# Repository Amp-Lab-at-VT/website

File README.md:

# Developing the Amp Lab website

Hello student of faculty! Welcome to the Amp Lab website repository. This is a simple static website built NextJS. It is hosted through Github Pages, making it easy to deploy and maintain. This document will guide you through the process of setting up your local development environment, making changes to the website, and deploying those changes.

You have two options for working on this locally: Docker, or Node. The following will describe both methods

# Using Docker

1. **Install Docker**: If you don't have Docker installed, download and install it from the [Docker website](https://www.docker.com/get-started).
2. **Clone the repository**: Open a terminal and run the following command to clone the repository
3. **Build and Run the Docker container**: Navigate to the cloned repository and run the following command to build and run the Docker container:
   ```bash
   docker-compose up --build
   ```

   And that's it!

# Using Node

1. **Install NVM**: If you don't have NVM installed, download and install it from the [NVM for Windows website](https://github.com/coreybutler/nvm-windows)
2.**Restart your computer to apply the changes**: After installing NVM, restart your computer to ensure that the changes take effect.
2. **Install Node**: Open a terminal and run the following command to install Node:
   ```bash
   nvm install 22
   nvm use 22
   ```

# Installing Dependencies
1. **Clone the repository**: Open a terminal and run the following command to clone the repository
   ```bash
   npm install
   ```

# Branch Before You Start Working
1. **Create a new branch**: Before making any changes, create a new branch for your work. This will help keep the main branch clean and allow for easier collaboration. Run the following command to create a new branch:
   ```bash
   git checkout -b your-branch-name
   ```

# Start the development server: Run the following command to start the development server:
   ```bash
   npm run dev
   ```

   This will start the development server and open the website in your default web browser. You can now make changes to the code and see them reflected in real-time.

# Pushing and PR Process
1. **Commit your changes**: After making changes, commit them to your branch with a descriptive message. Run the following command to commit your changes:
   ```bash
   git add .
   git commit -m "Your commit message"
   ```
2. Push your changes: Push your changes to the remote repository with the following command:
   ```bash
   git push origin your-branch-name
   ```
3. **Create a pull request**: Go to the GitHub repository and create a pull request from your branch to the main branch. This will allow others to review your changes before merging them into the main branch.
4. **Review and merge**: Once your pull request is approved, you can merge it into the main branch. This will update the main branch with your changes.

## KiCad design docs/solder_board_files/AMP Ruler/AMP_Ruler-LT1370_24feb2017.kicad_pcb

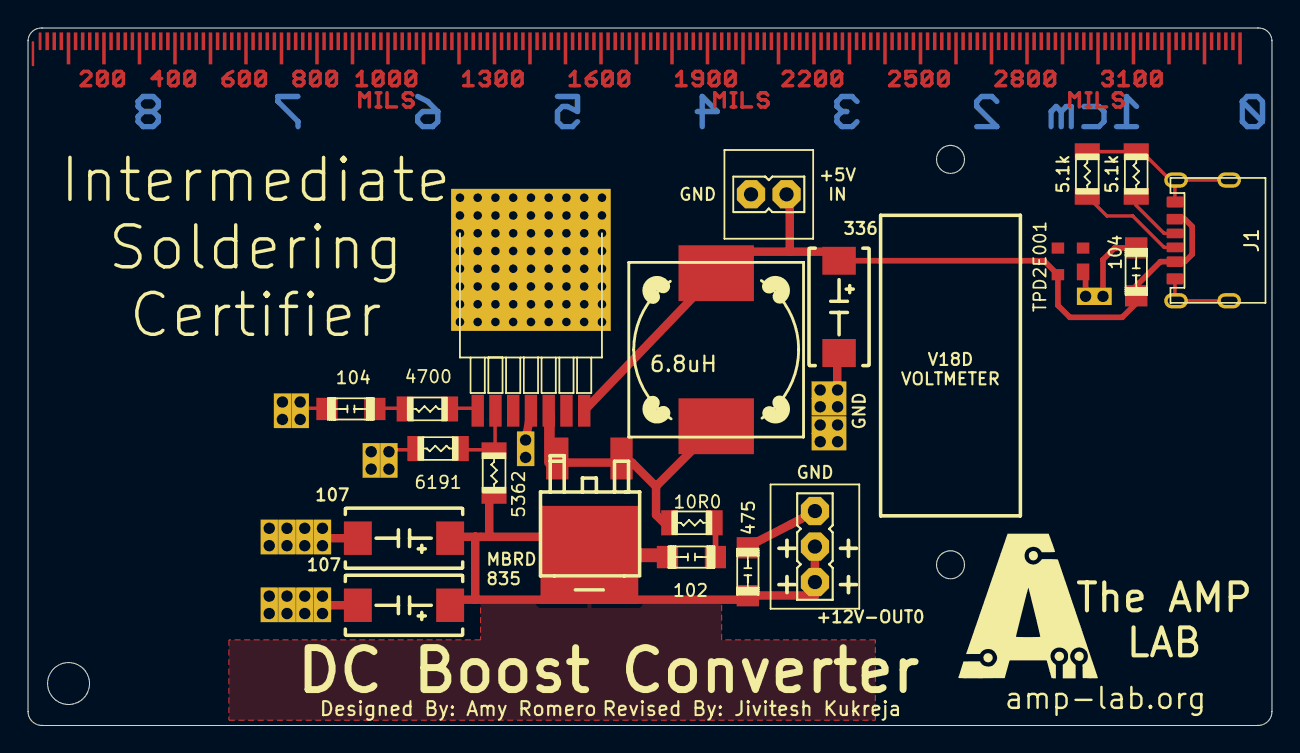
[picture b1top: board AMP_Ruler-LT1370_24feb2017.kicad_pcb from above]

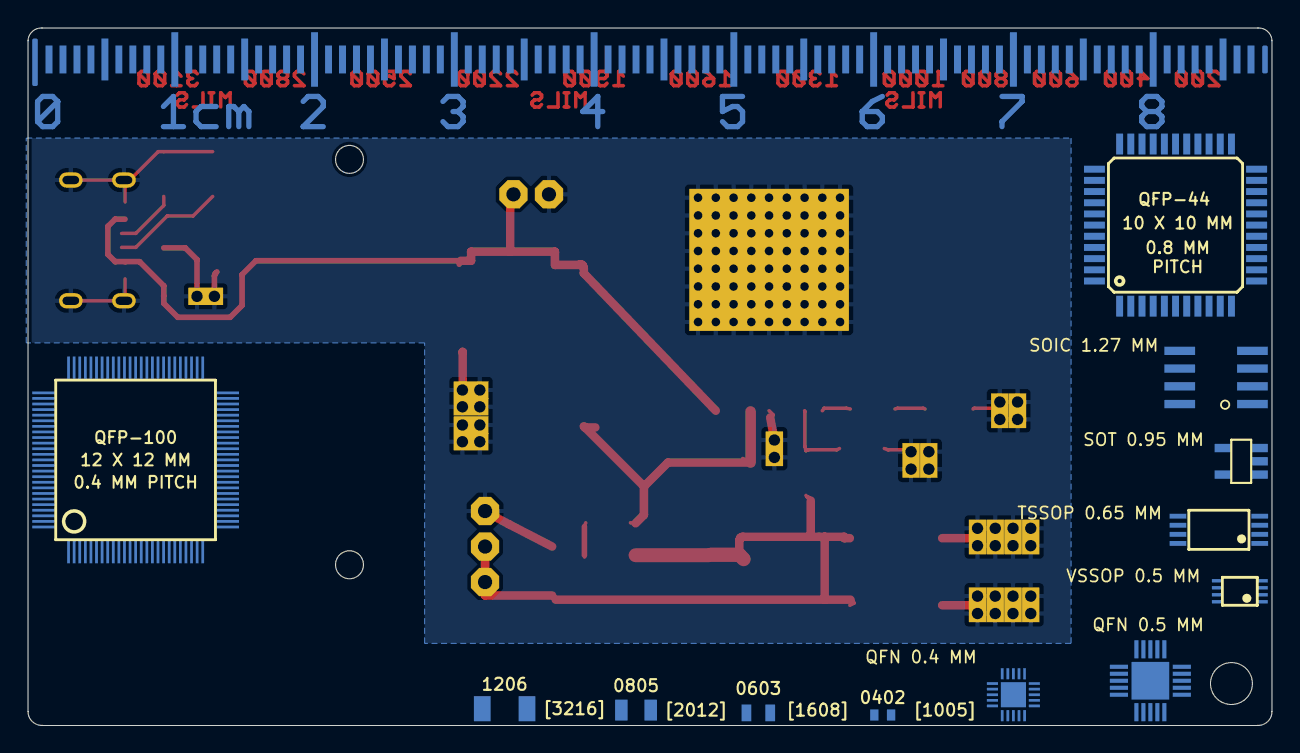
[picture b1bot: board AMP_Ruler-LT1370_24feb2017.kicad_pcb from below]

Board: 2 copper layers, 89.0 x 49.9 mm, 55 parts (19 on the bottom side), 10 nets.

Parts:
+12V-OUT0: FE03-1-TB
---0: DIODE-DPAK
@HOLE0, @HOLE1, @HOLE2: (no value)
C1: 336; C-2917
C2, C3: 107; C-2917
C4, C5: 104; C-1206
C6: 475; C-1206
C7: 102; C-1206
GND0: DOUBLE_RF_VIA
J1: USB_C_Receptacle_USB2.0; GCTUSB4125GFA190
L1: 6.8uH; SRR1240
R1: 6191; R1206
R2: 5362; R1206
R3, R6: 5.1k; R1206
R4: 4700; R1206
R5: 10R0; R1206
U1: LT1370
U$1: SOIC 1.27 MM; SOIC-8
U$2: SOT 0.95 MM; SOT23-5
U$3: TSSOP 0.65 MM; TSSOP-8
U$4: VSSOP 0.5 MM; VSSOP-8
U$5: QFP-44-10X10; QFP-44
U$6: QFP-100-12X12; QFP-100
U$8: QFN 0.5 MM; QFN-20-4X4
U$9: QFN 0.4 MM; QFN-20-3X3
U$10: 1206; R1206
U$11: 0805; R0805
U$12: 0603; R0603
U$13: 0402; R0402
U$14: MMRULER
U$15: MILRULER
U$16, U$17, U$18, U$19, U$20, U$21, U$22, U$23, U$24, U$25, U$26, U$27, U$32, U$33, U$34, U$35, U$37: DOUBLE_RF_VIA
U$36: TPD2E001; SOT-143
U$38: FE02-TB

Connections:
/AMP_Ruler-LT1370_24feb2017_3/VIN: C1.P$1, C4.P$2, J1.A9 (VBUS), J1.B9 (VBUS), L1.1, U1.P$7 (VIN), U$36.4 (+), U$38.1
/AMP_Ruler-LT1370_24feb2017_3/VOUT: +12V-OUT0.1, +12V-OUT0.2, ---0.P$4, C2.P$1, C3.P$1, C6.P$2, C7.P$1, R2.2
GND: +12V-OUT0.3, C1.P$2, C2.P$2, C3.P$2, C4.P$1, C5.P$2, C6.P$1, GND0.1, GND0.2 (P1), J1.A12 (GND), J1.B12 (GND), J1.S1 (SHIELD), R1.1, R3.2, R6.2, U1.P$4 (GND), U1.P$8 (GNDT), U1.P$9 (GNDT), U1.P$10 (GNDT), U1.P$11 (GNDT), U1.P$12 (GNDT), U1.P$13 (GNDT), U1.P$14 (GNDT), U1.P$15 (GNDT), U1.P$16 (GNDT), U1.P$17 (GNDT), U1.P$18 (GNDT), U1.P$19 (GNDT), U1.P$20 (GNDT), U1.P$21 (GNDT), U1.P$22 (GNDT), U1.P$23 (GNDT), U1.P$24 (GNDT), U1.P$25 (GNDT), U1.P$26 (GNDT), U1.P$27 (GNDT), U1.P$28 (GNDT), U1.P$29 (GNDT), U1.P$30 (GNDT), U1.P$31 (GNDT), U1.P$32 (GNDT), U1.P$33 (GNDT), U1.P$34 (GNDT), U1.P$35 (GNDT), U1.P$36 (GNDT), U1.P$37 (GNDT), U1.P$38 (GNDT), U1.P$39 (GNDT), U1.P$40 (GNDT), U1.P$41 (GNDT), U1.P$42 (GNDT), U1.P$43 (GNDT), U1.P$44 (GNDT), U1.P$45 (GNDT), U1.P$46 (GNDT), U1.P$47 (GNDT), U1.P$48 (GNDT), U1.P$49 (GNDT), U1.P$50 (GNDT), U1.P$51 (GNDT), U1.P$52 (GNDT), U1.P$53 (GNDT), U1.P$54 (GNDT), U1.P$55 (GNDT), U1.P$56 (GNDT), U1.P$57 (GNDT), U1.P$58 (GNDT), U1.P$59 (GNDT), U1.P$60 (GNDT), U1.P$61 (GNDT), U1.P$62 (GNDT), U1.P$63 (GNDT), U1.P$64 (GNDT), U1.P$65 (GNDT), U1.P$66 (GNDT), U1.P$67 (GNDT), U1.P$68 (GNDT), U1.P$69 (GNDT), U1.P$70 (GNDT), U1.P$71 (GNDT), U1.P$72 (GNDT), U1.P$73 (GNDT), U1.P$75 (GNDT), U1.P$76 (GNDT), U1.P$77 (GNDT), U1.P$78 (GNDT), U1.P$79 (GNDT), U1.P$80 (GNDT), U$16.1, U$16.2 (P1), U$17.1, U$17.2 (P1), U$18.1, U$18.2 (P1), U$19.1, U$19.2 (P1), U$20.1, U$20.2 (P1), U$21.1, U$21.2 (P1), U$22.1, U$22.2 (P1), U$23.1, U$23.2 (P1), U$24.1, U$24.2 (P1), U$25.1, U$25.2 (P1), U$26.1, U$26.2 (P1), U$27.1, U$27.2 (P1), U$32.1, U$32.2 (P1), U$33.1, U$33.2 (P1), U$34.1, U$34.2 (P1), U$35.1, U$35.2 (P1), U$36.1 (-), U$37.1, U$37.2 (P1), U$38.2
unnamed: ---0.P$1, ---0.P$3, L1.2, R5.1, U1.P$5 (VSW)
unnamed: C5.P$1, R4.2
unnamed: C7.P$2, R5.2
unnamed: J1.A5 (CC1), R6.1
unnamed: J1.B5 (CC2), R3.1
unnamed: R1.2, R2.1, U1.P$2 (FB)
unnamed: R4.1, U1.P$1 (VC)

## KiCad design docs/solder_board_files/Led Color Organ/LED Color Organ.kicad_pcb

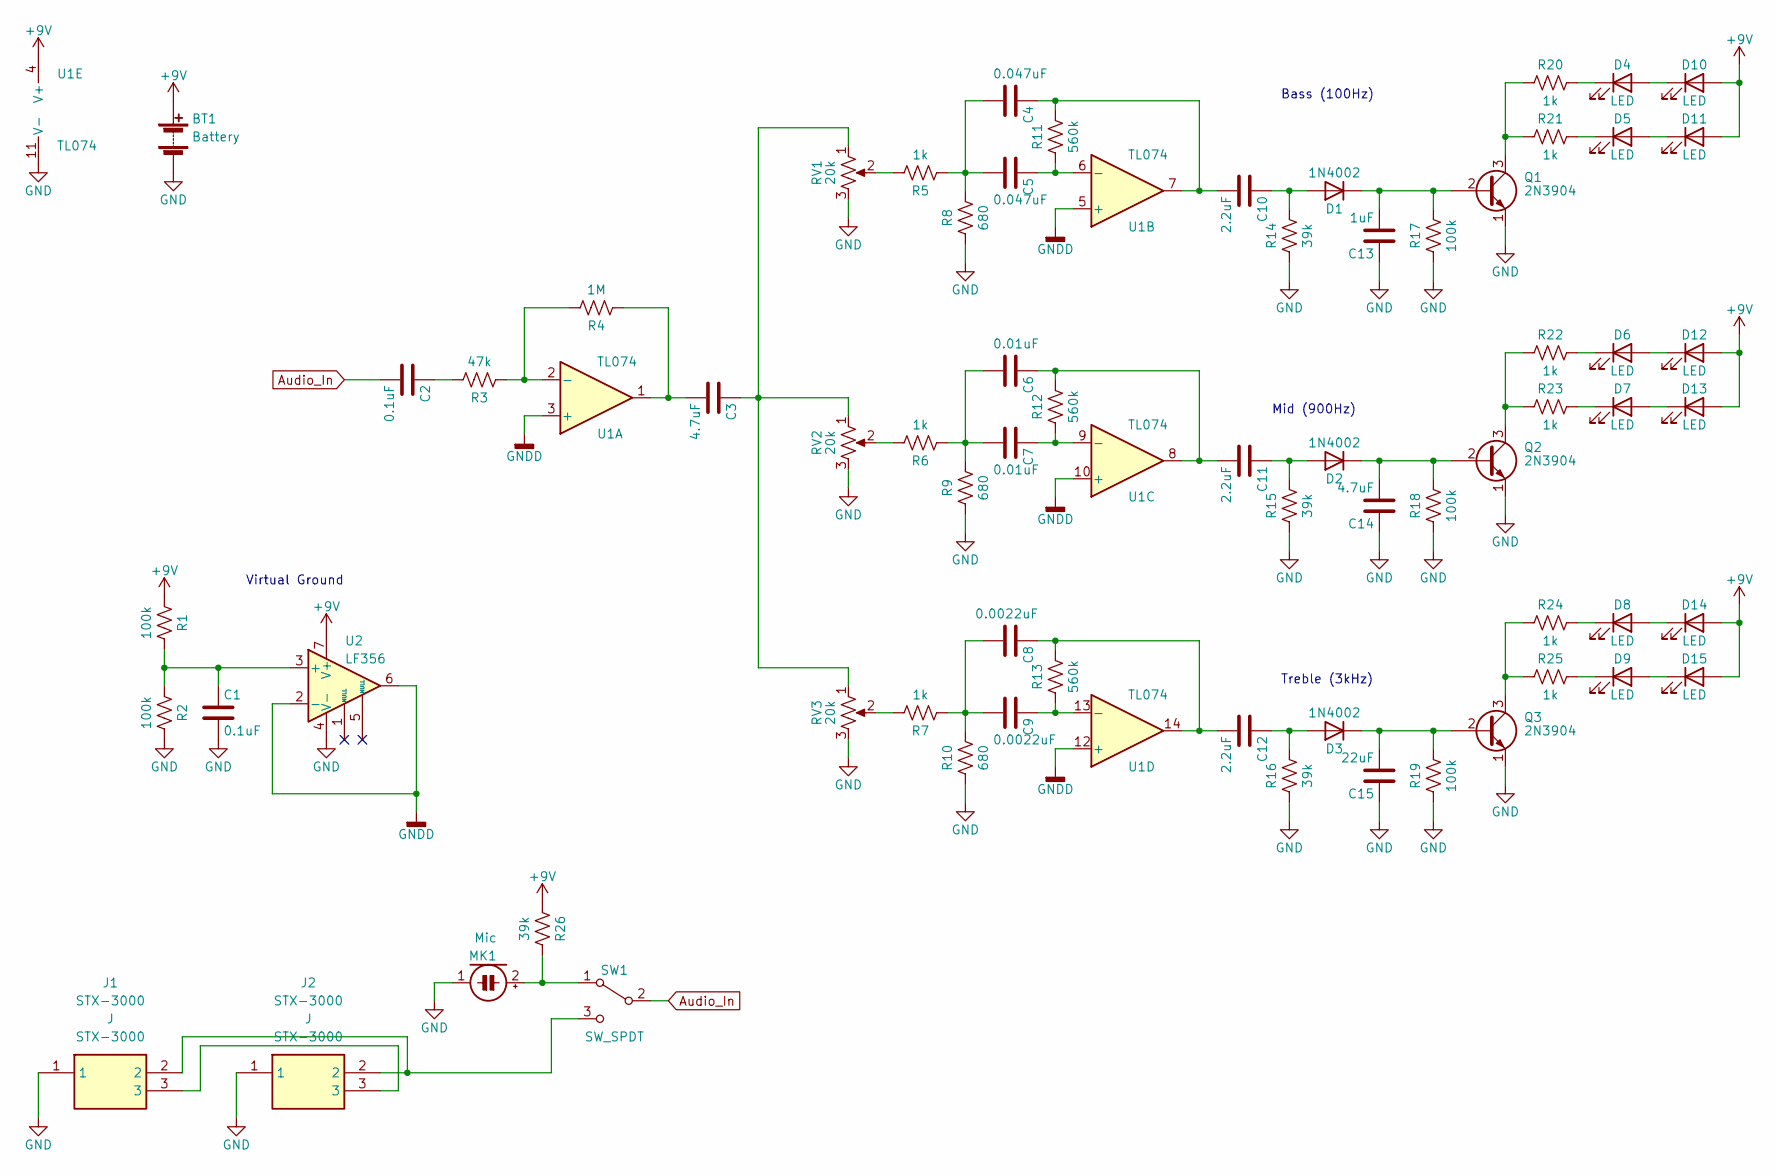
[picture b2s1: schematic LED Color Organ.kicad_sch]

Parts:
BT1: Battery; PinHeader_1x02_P2.54mm_Vertical_Battery; Digikey PN 36-232-ND
C1, C2: 0.1uF; C_Disc_D4.3mm_W1.9mm_P5.00mm_Handsolder; Digikey PN 399-9877-1-ND
C3, C14: 4.7uF; C_Disc_D4.3mm_W1.9mm_P5.00mm_Handsolder; Digikey PN 445-173577-1-ND
C4, C5: 0.047uF; C_Disc_D4.3mm_W1.9mm_P5.00mm_Handsolder; Digikey PN 445-173451-1-ND
C6, C7: 0.01uF; C_Disc_D4.3mm_W1.9mm_P5.00mm_Handsolder; Digikey PN 445-173384-1-ND
C8, C9: 0.0022uF; C_Disc_D4.3mm_W1.9mm_P5.00mm_Handsolder; Digikey PN 445-173353-1-ND
C10, C11, C12: 2.2uF; C_Disc_D4.3mm_W1.9mm_P5.00mm_Handsolder; Digikey PN 445-173575-1-ND
C13: 1uF; C_Disc_D4.3mm_W1.9mm_P5.00mm_Handsolder; Digikey PN 445-173579-1-ND
C15: 22uF; C_Disc_D4.3mm_W1.9mm_P5.00mm_Handsolder; Digikey PN 445-173367-1-ND
D1, D2, D3: 1N4002; D_DO-41_SOD81_P10.16mm_Horizontal_HandSolder; Digikey PN 1N4002-TPMSCT-ND
D4, D5, D6, D7, D8, D9, D10, D11, D12, D13, D14, D15: LED; LED_D5.0mm_handsolder
J1, J2: STX-3000; STX3000; Mouser Part Number 806-STX-3000
MK1: Mic; CUI_CMA-6542PF; Digikey PN 102-1720-ND
Q1, Q2, Q3: 2N3904; TO-92_HandSolder; Digikey PN 2N3904FS-ND
R1, R2, R17, R18, R19: 100k; R_Combo; Digikey PN CF18JT100KCT-ND
R3: 47k; R_Combo; Digikey PN S47KQCT-ND
R4: 1M; R_Combo; Digikey PN CF18JT1M00CT-ND
R5, R6, R7, R20, R21, R22, R23, R24, R25: 1k; R_Combo; Digikey PN CF18JT1K00CT-ND
R8, R9, R10: 680; R_Combo; Digikey PN CF18JT680RCT-ND
R11, R12, R13: 560k; R_Combo; Digikey PN CF18JT560KCT-ND
R14, R15, R16, R26: 39k; R_Combo; Digikey PN CF18JT39K0CT-ND
RV1, RV2, RV3: 20k; POT_Bourns_3306F; Digikey PN 3306F-203-ND
SW1: SW_SPDT; SW_OS102011MS2QN1; Digikey PN CKN9565-ND
U1: TL074; DIP-14_labeled; Digikey PN 296-1777-ND
U2: LF356; DIP-8_labeled; Digikey PN LF356N/NOPB-ND

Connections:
+9V: BT1.1 (+), D10.2 (A), D11.2 (A), D12.2 (A), D13.2 (A), D14.2 (A), D15.2 (A), R1.1, R26.1, U1.4 (V+), U2.7 (V+)
Audio_In: C2.2, SW1.2 (B)
GND: BT1.2 (-), C1.2, C13.1, C14.1, C15.1, J1.1, J2.1, MK1.1 (-), Q1.1 (E), Q2.1 (E), Q3.1 (E), R2.2, R8.1, R9.1, R10.1, R14.1, R15.1, R16.1, R17.1, R18.1, R19.1, RV1.3, RV2.3, RV3.3, U1.11 (V-), U2.4 (V-)
GNDD: U1.3 (+), U1.5 (+), U1.10 (+), U1.12 (+), U2.2 (-), U2.6
unnamed: C1.1, R1.2, R2.1, U2.3 (+)
unnamed: C2.1, R3.2
unnamed: C3.1, RV1.1, RV2.1, RV3.1
unnamed: C3.2, R4.1, U1.1
unnamed: C4.2, C5.2, R5.1, R8.2
unnamed: C5.1, R11.1, U1.6 (-)
unnamed: C6.2, C7.2, R6.1, R9.2
unnamed: C7.1, R12.1, U1.9 (-)
unnamed: C8.2, C9.2, R7.1, R10.2
unnamed: C9.1, R13.1, U1.13 (-)
unnamed: C10.1, D1.2 (A), R14.2
unnamed: C4.1, C10.2, R11.2, U1.7
unnamed: C11.1, D2.2 (A), R15.2
unnamed: C6.1, C11.2, R12.2, U1.8
unnamed: C12.1, D3.2 (A), R16.2
unnamed: C8.1, C12.2, R13.2, U1.14
unnamed: C13.2, D1.1 (K), Q1.2 (B), R17.2
unnamed: C14.2, D2.1 (K), Q2.2 (B), R18.2
unnamed: C15.2, D3.1 (K), Q3.2 (B), R19.2
unnamed: D4.1 (K), R20.2
unnamed: D5.1 (K), R21.2
unnamed: D6.1 (K), R22.2
unnamed: D7.1 (K), R23.2
unnamed: D8.1 (K), R24.2
unnamed: D9.1 (K), R25.2
unnamed: D4.2 (A), D10.1 (K)
unnamed: D5.2 (A), D11.1 (K)
unnamed: D6.2 (A), D12.1 (K)
unnamed: D7.2 (A), D13.1 (K)
unnamed: D8.2 (A), D14.1 (K)
unnamed: D9.2 (A), D15.1 (K)
unnamed: J1.2, J2.2, SW1.3 (C)
unnamed: J1.3, J2.3
unnamed: MK1.2 (+), R26.2, SW1.1 (A)
unnamed: Q1.3 (C), R20.1, R21.1
unnamed: Q2.3 (C), R22.1, R23.1
unnamed: Q3.3 (C), R24.1, R25.1
unnamed: R3.1, R4.2, U1.2 (-)
unnamed: R5.2, RV1.2
unnamed: R6.2, RV2.2
unnamed: R7.2, RV3.2

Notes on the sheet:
Virtual Ground
Bass (100Hz)
Mid (900Hz)
Treble (3kHz)

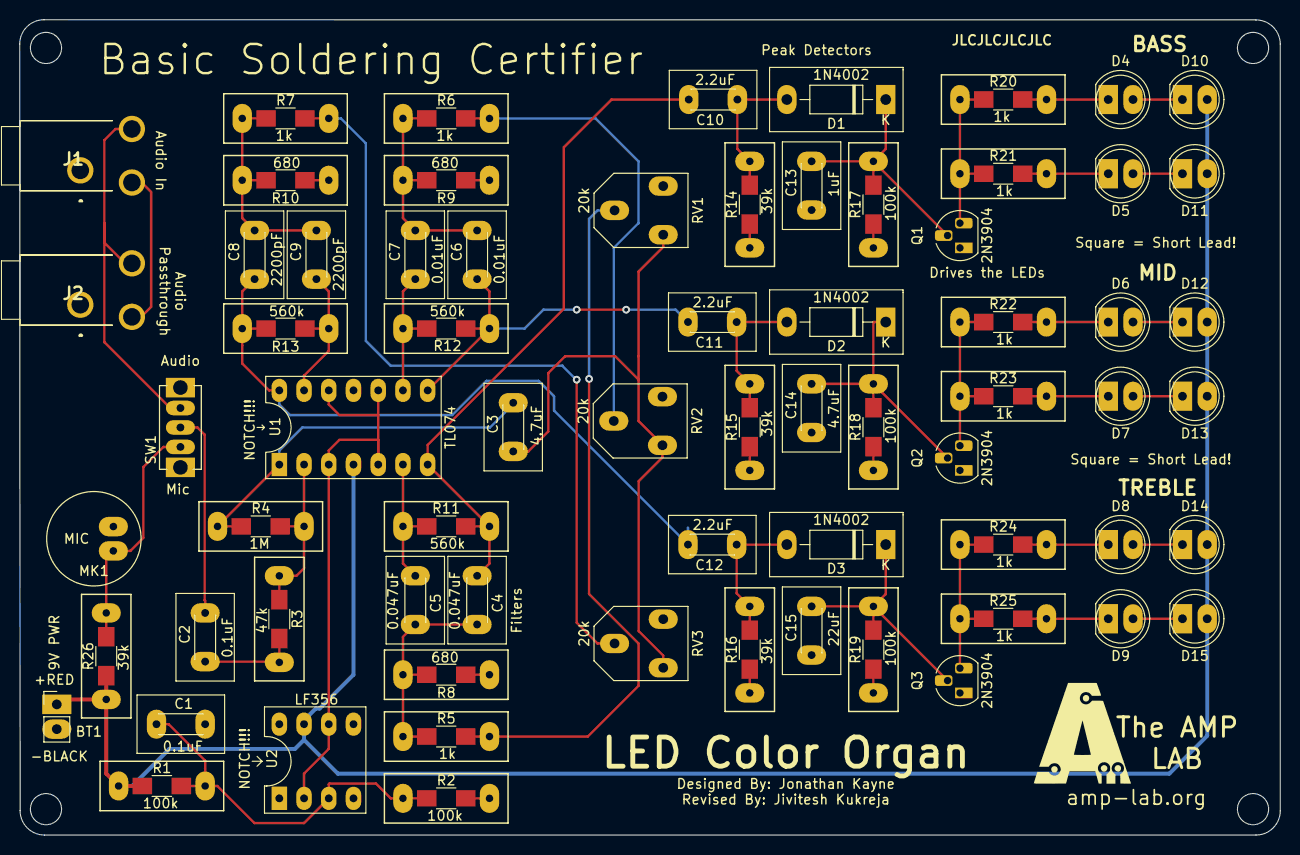
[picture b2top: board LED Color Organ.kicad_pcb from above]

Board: 2 copper layers, 129.5 x 83.8 mm, 69 parts (0 on the bottom side), 45 nets.

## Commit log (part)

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2023-04-19 PR#67: Updates to Project Rendering
    * Image additions
    * New projects
    * Updated project page
    ---------
2023-04-27 Adding devnotes
2023-04-27 Small updates
2023-04-27 Adding in mentors for projects
2023-04-28 Added ability to search through projects, as well we better mobile formatting @Ethan
2023-04-28 Cleanup
2023-04-28 PR#68: Search and Better Project Mobile Formatting
    * Adding devnotes
    * Adding in mentors for projects
    * Added ability to search through projects, as well we better mobile formatting @Ethan
    * Cleanup
2023-04-28 PR#64: Adding the Cockcroft-Walton circuit project
    Update repos.yaml
2023-04-28 New things
2023-04-28 PR#69: FPV Car to repos.yaml
    Adding in a project
2023-04-29 New Documentation
2023-04-29 Updating for better visability of how to begin, especially for less git-savy members
2023-04-29 PR#70: Better Documentation to Start a Project without a local repo
    * New Documentation
    * Updating for better visability of how to begin, especially for less git-savy members
2023-04-30 Sorting active and inactive projects
2023-05-01 Sorting by last commit enabled
2023-05-01 Sorts the Projects into Active and Inactive, based on a timeout (#71)
    * Sorting active and inactive projects
    * Sorting by last commit enabled
2023-05-01 Made updates to the Mentors
2023-05-02 add Instrument Looper project
2023-05-02 fix branch name for Instrument Looper project
2023-05-02 Bump yaml from 2.2.1 to 2.2.2
    Bumps [yaml](https://github.com/eemeli/yaml) from 2.2.1 to 2.2.2.
    - [Release notes](https://github.com/eemeli/yaml/releases)
    - [Commits](https://github.com/eemeli/yaml/compare/v2.2.1...v2.2.2)
    ---
    updated-dependencies:
    - dependency-name: yaml
2023-05-03 Small tweaks and security updates
2023-05-03 Tweaks to getting started page
2023-05-03 PR#77" Bump yaml from 2.2.1 to 2.2.2, as well as formatting changes
    Bumps [yaml](https://github.com/eemeli/yaml) from 2.2.1 to 2.2.2.
    - [Release notes](https://github.com/eemeli/yaml/releases)
    - [Commits](https://github.com/eemeli/yaml/compare/v2.2.1...v2.2.2)
    ---
    updated-dependencies:
    - dependency-name: yaml
2023-05-06 New Favicon
2023-05-08 Footer updates to reroute to leadershup page
2023-05-08 PR#78: Better Favicon and Footer
    * New Favicon
    * Footer updates to reroute to leadership page
2023-05-17 Adding in water bottle project
2023-05-17 PR#79: Adding Smart Water Bottle Project to website
    Adding in water bottle project with added formatting
2023-05-17 Beginning to improve search
2023-05-18 Fixed search to show active and inactive projects
2023-05-18 PR#80: Improved Search
    Improved Search
2023-05-18 Revert "PR#80: Improved Search"
    This reverts commit 9850a0361891686ea5b4ab436a06d4160d889d5a.
2023-05-18 PR#81: Revert Search to fix linting errors
2023-05-18 Cleared linting error
2023-05-18 PR#82: Improved Search, with new linting rule
    Improved Search
2023-05-18 Adding in more resources
2023-05-18 #83: Resources for Mentees and Mentors
    More Resources
2023-06-12 Updating parallax
2023-06-13 [WIP
2023-06-13 pretty much done
2023-06-13 final?
    I believe this is good enough for now to merge.
2023-06-13 format code (class -> className)
2023-06-14 [WIP] probably done
2023-06-14 markdown lint
2023-06-20 initial test (WIP, messy code)
2023-06-20 fix Box.jsx summary text length
2023-06-25 Add DAW project to repos.yaml
2023-06-25 Add DAW project to repos.yaml (#88)
2023-07-05 New project from Henry Forsyth
2023-07-10 Update repos.yaml
    Added Protoglove to website
2023-07-16 Added Protoglove to website (#91)
    Added Protoglove to website
2023-08-18 fix typo
2023-08-21 Marc Project
2023-08-21 Marc Project (#92)
2023-08-27 added new soldering
2023-08-30 All the things
2023-08-30 (#93) Added New Soldering Curriculum
    * added new soldering
    * All the things
    ---------
2023-08-30 New href
2023-08-30 New href (#94)
2023-08-30 revert md checkbox to html
2023-09-11 PR Template
2023-09-11 Updated assignees
2023-09-11 Project link
2023-09-11 Task/project traceability (#95)
    * PR Template
    * Updates
    * Updated assignees
    * Project link
2023-09-11 All new
2023-09-11 Bug fixes (#96)
    All new
2023-10-05 added new sold. cur.
2023-10-17 Adding New Soldering Curriculum (#117)
2023-10-17 New workflow to validate build
2023-10-17 Dunno
2023-10-17 Just npm
2023-10-17 Let's do this
2023-10-17 New workflow to validate build (#118)
    * New workflow to validate build
2023-10-23 Update repos.yaml
    Adding Temperature Controlled Fan to the Website of Listed Projects
2023-10-24 Sponsorship page
2023-10-24 Bad me, forgot the keys:
2023-10-24 Added Analog Guitar Amplifier With Effects to repos.yaml
2023-10-24 Yaml Checker
2023-10-24 All the things'
2023-10-24 New test
2023-10-24 New Phase
2023-10-24 Checkout
2023-10-24 Pytest
2023-10-24 Name
2023-10-24 Task/yaml checker (#122)
    * Yaml Checker
2023-10-24 Update repos.yaml (#119)
    Adding Temperature Controlled Fan to the Website of Listed Projects
2023-10-25 New workflow??
2023-10-25 removing access token
2023-10-25 New workflow
2023-10-25 Testing
2023-10-25 Crap
2023-10-25 JUST BUILD!!!
2023-10-25 Spelling
2023-10-25 Sponsorship Page (#120)
2023-10-25 Leadership
2023-10-25 Tweaks to sponsorship page (#123)
2023-10-25 just testing out git with the projects file
2023-10-25 testing it again lol
2023-11-16 Rules
2023-11-19 Updated rules
2023-11-20 Rules (#127)
2023-11-27 fixed adv sol req
2023-11-27 fixed adv sol req (#128)
2024-01-06 Test
2024-01-06 All the files
2024-01-06 Adding MDE documents to the website for Toby (#130)
2024-01-06 Booking on website
2024-01-07 Booking on website (#131)
2024-01-07 Warning
2024-01-07 Uninstall
2024-01-07 Better callout
2024-01-16 Swipe access documents, with some formatting
2024-01-16 Swipe access documents, with some formatting (#133)
2024-01-16 Patch
2024-01-16 Patch (#134)
2024-01-26 new sol worl
2024-01-26 Adding
2024-01-26 Updating MDE Things (#137)
2024-01-28 Formatted
2024-01-28 Getting rid of duplicate import
2024-01-28 Soldering Training Updates (#132)
2024-01-29 fixed soldering manual links
2024-01-29 fixed additional links
2024-02-18 changed sold pages
2024-02-19 use typescript and state mantine UI
2024-02-19 hotfix
2024-02-20 example on how to use mantine
2024-02-20 New Soldering Pages (#144)
    Could you look into why int and adv pages are being cut by the footer?
    ---------
2024-02-24 JIVI!!!!!!!!!!!!!!!!!!!!!
2024-02-24 Github
2024-02-24 Updates to Soldering Links (#147)
2024-02-24 Bookings fix
2024-02-24 Bookings fix (#148)
2024-03-06 mdx instead of md
2024-03-06 reset locations
2024-03-09 added advnace board files
2024-03-17 addAdvSolFiles
2024-03-17 addAdvSolFiles (#152)
2024-03-28 as const
2024-03-28 almost done
2024-04-05 Modifiying Repos Yaml to include more projects
    modifying repos yaml to include more pictures
2024-04-09 Add projects to repos.yaml
2024-04-10 Add projects to repos.yaml (#155)
    Adding 2 projects
2024-04-11 fix merge
2024-04-11 fix errors
2024-04-15 Add breadboard graphics card project
2024-04-15 Add GPU Project (#156)
    see above
2024-08-18 Update repos.yaml
    Add project
2024-08-18 Update repos.yaml (#159)
    Add project
2024-08-30 Latest
2024-08-30 Fixing 404 (#161)
2024-09-27 Update repos.yaml
    Adding another Mentee's project to the website
2024-09-29 New format
2024-09-29 Updates to help Ethan
2024-09-29 Tyler
2024-09-29 Updated Leadership Page
2024-10-08 Markdown updates
2024-10-09 Add laser cutter documentation
2024-10-09 Monitor page
2024-10-18 Add Matthew's project to repos.yaml
2025-01-19 update to app router + next15 + react19
2025-01-19 Typescipt, Next15, React19, Mantine UI
2025-02-01 Updating deps
2025-02-02 Fixing builder
2025-02-02 Updating poetry
2025-02-17 Add Portable Blood Pressure Monitoring Device to repos.yaml
2025-02-18 chat i put myself on the leadership page as a mentor
2025-02-18 Still check yaml
2025-02-18 Updating poetry version
2025-02-18 Updates to darkmode context
2025-02-18 Adding tyler back
2025-02-24 Mentor Correction
2025-05-14 practice
2025-05-14 Updates to notes and docker deployment
2025-08-27 updating sign up process
2025-08-27 fix for ci cd
2025-08-27 updating new members
2025-09-08 update leadership
2025-09-08 leadership page update
2025-09-17 leadership change test
2025-09-17 alumni section added
2025-09-18 Initial plan
2025-09-18 Phase 1 & 2 Complete: Modern design system and enhanced UX
2025-09-18 Complete website modernization: Enhanced projects page and cross-page consistency
2025-09-19 soldering trainers added
2025-10-02 updated swipe access
2025-10-02 Updated lab training guide
2025-10-02 updated swipe access policy
2026-03-08 updated project display logic
2026-03-08 fixed ci cd
2026-03-08 fixed cicd
2026-03-08 added projects script
2026-03-09 Add new projects to repos.yaml
2026-03-10 added projects
2026-06-02 Added headshots
2026-06-03 attempted to fix bug
2026-06-03 oops
2026-06-04 Fix typos in Leadership component
2026-06-14 Rename � to error
2026-06-14 update the docs
2026-06-14 change theme color
2026-06-15 update documents page + upload safty datasheet
2026-06-15 leadership color fix
2026-06-15 add and update lab hygiene page
2026-06-15 add and update sponsorship page
2026-06-15 fix documentation issue
2026-06-15 clean the code
2026-06-17 Misc Updates
